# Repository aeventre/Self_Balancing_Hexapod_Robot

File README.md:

View this project on [CADLAB.io](https://cadlab.io/project/29567). 

# Self-Balancing Hexapod Robot
Created by: **Alec Ventresca & Ella Hicks**  

## Table of Contents
 - **[Self-Balancing Hexapod Robot](#self-balancing-hexapod-robot)**
   - [Overview](#overview)
   - [Future Ideas/Plans](#future-ideas)
   - [Acknowledgments](#acknowledgments) 
- [**Software Design**](ros2_ws/README.md)
  - [Overview](ros2_ws/README.md#overview)
  - [Instructions for Running the Software on the Pi](ros2_ws/README.md#instructions-for-running-the-software-on-the-pi)
    - [1. Setting Up the Virtual Environment](ros2_ws/README.md#1-setting-up-the-virtual-environment)
    - [2. Commands for Running Nodes](ros2_ws/README.md#2-commands-for-running-nodes)
  - [ROS2 Package Overview](ros2_ws/README.md#ros2-package-overview)
    - [1. Support Polygon Calculator](ros2_ws/README.md#1-support-polygon-calculator)
    - [2. Servo Control](ros2_ws/README.md#2-servo-control)
    - [3. IMU Interface](ros2_ws/README.md#3-imu-interface)
    - [4. Foot Sensor Package](ros2_ws/README.md#4-foot-sensor-package)
    - [5. Static Balancing Package](ros2_ws/README.md#5-static-balancing-package)
    - [6. Inverse and Forward Kinematics Package](ros2_ws/README.md#6-inverse-and-forward-kinematics-package)
    - [7. Center of Mass Calculator Package](ros2_ws/README.md#7-center-of-mass-calculator-package)
  - [ROS2 Topic List](ros2_ws/README.md#ros2-topic-list)
- [**Hardware Design**](hardware/README.md) 
  - [Overview](hardware/README.md#overview)
  - [Structure](hardware/README.md#structure)
  - [Electronics](hardware/README.md#electronics)
    - [Setting the I2C Address of the PCA9685](hardware/README.md#setting-the-i2c-address-of-the-pca9685)
  - [PCB Layout](hardware/README.md#pcb-layout)

## Overview
This robot was created to be a platform for us to learn and experiment with various types of sensors and gaits as well as learn the ROS2 framework. Modularity is a large component of this design, both hardware and software wise, so different sensors can be added and removed without needing to change the core design of the robot. Currently, this is just the foundation of the robot and we intend to add more sensor and package configurations in the future!  

The goal for the initial configuration of this project was to design a Hexapod Robot capable of performing dynamic movements and maintaining self-balance. The robot demonstrates the integration of mechanical and electronic systems and software packages to achieve autonomous and stable locomotion. The hexapod robot features a Raspberry Pi 4b as the central processing unit. It relies on ROS 2 Jazzy to manage the communication and control across the robot's various components. Each package communication ensures continuous data exchange between the packages for dynamic adjustments. The key objectives of the hexapod include the following:

1. Ensuring the robot can walk and move dynamically.
2. Incorporating real-time balancing mechanisms to keep the robot functional and upright under various conditions.
3. Develop modular software packages for control, movement computation, and sensing.
4. Utilize ROS 2 Jazzy to coordinate the robot's operations.

### Future Ideas
In no particular order:
1. Debugging the code and re-doing the math for the kinematics package to make it work efficiently.
2. Using a LiDAR sensor to map out a room for the robot.
3. Experimenting with different gaits (i.e. a quadruped "attack" mode).
4. Adding a Pi camera and learning opencv to have the robot recognize and go to people.
5. Implementing rough terrain navigation.

## Acknowledgments
All CAD models used are from "Robs Tech Workbench" at https://github.com/robs-tech-workbench/hexapod_spiderbot_model/
  
Shoutout to Addison Sears-Collins for all the incredibly helpful ROS2 tutorials at https://automaticaddison.com/

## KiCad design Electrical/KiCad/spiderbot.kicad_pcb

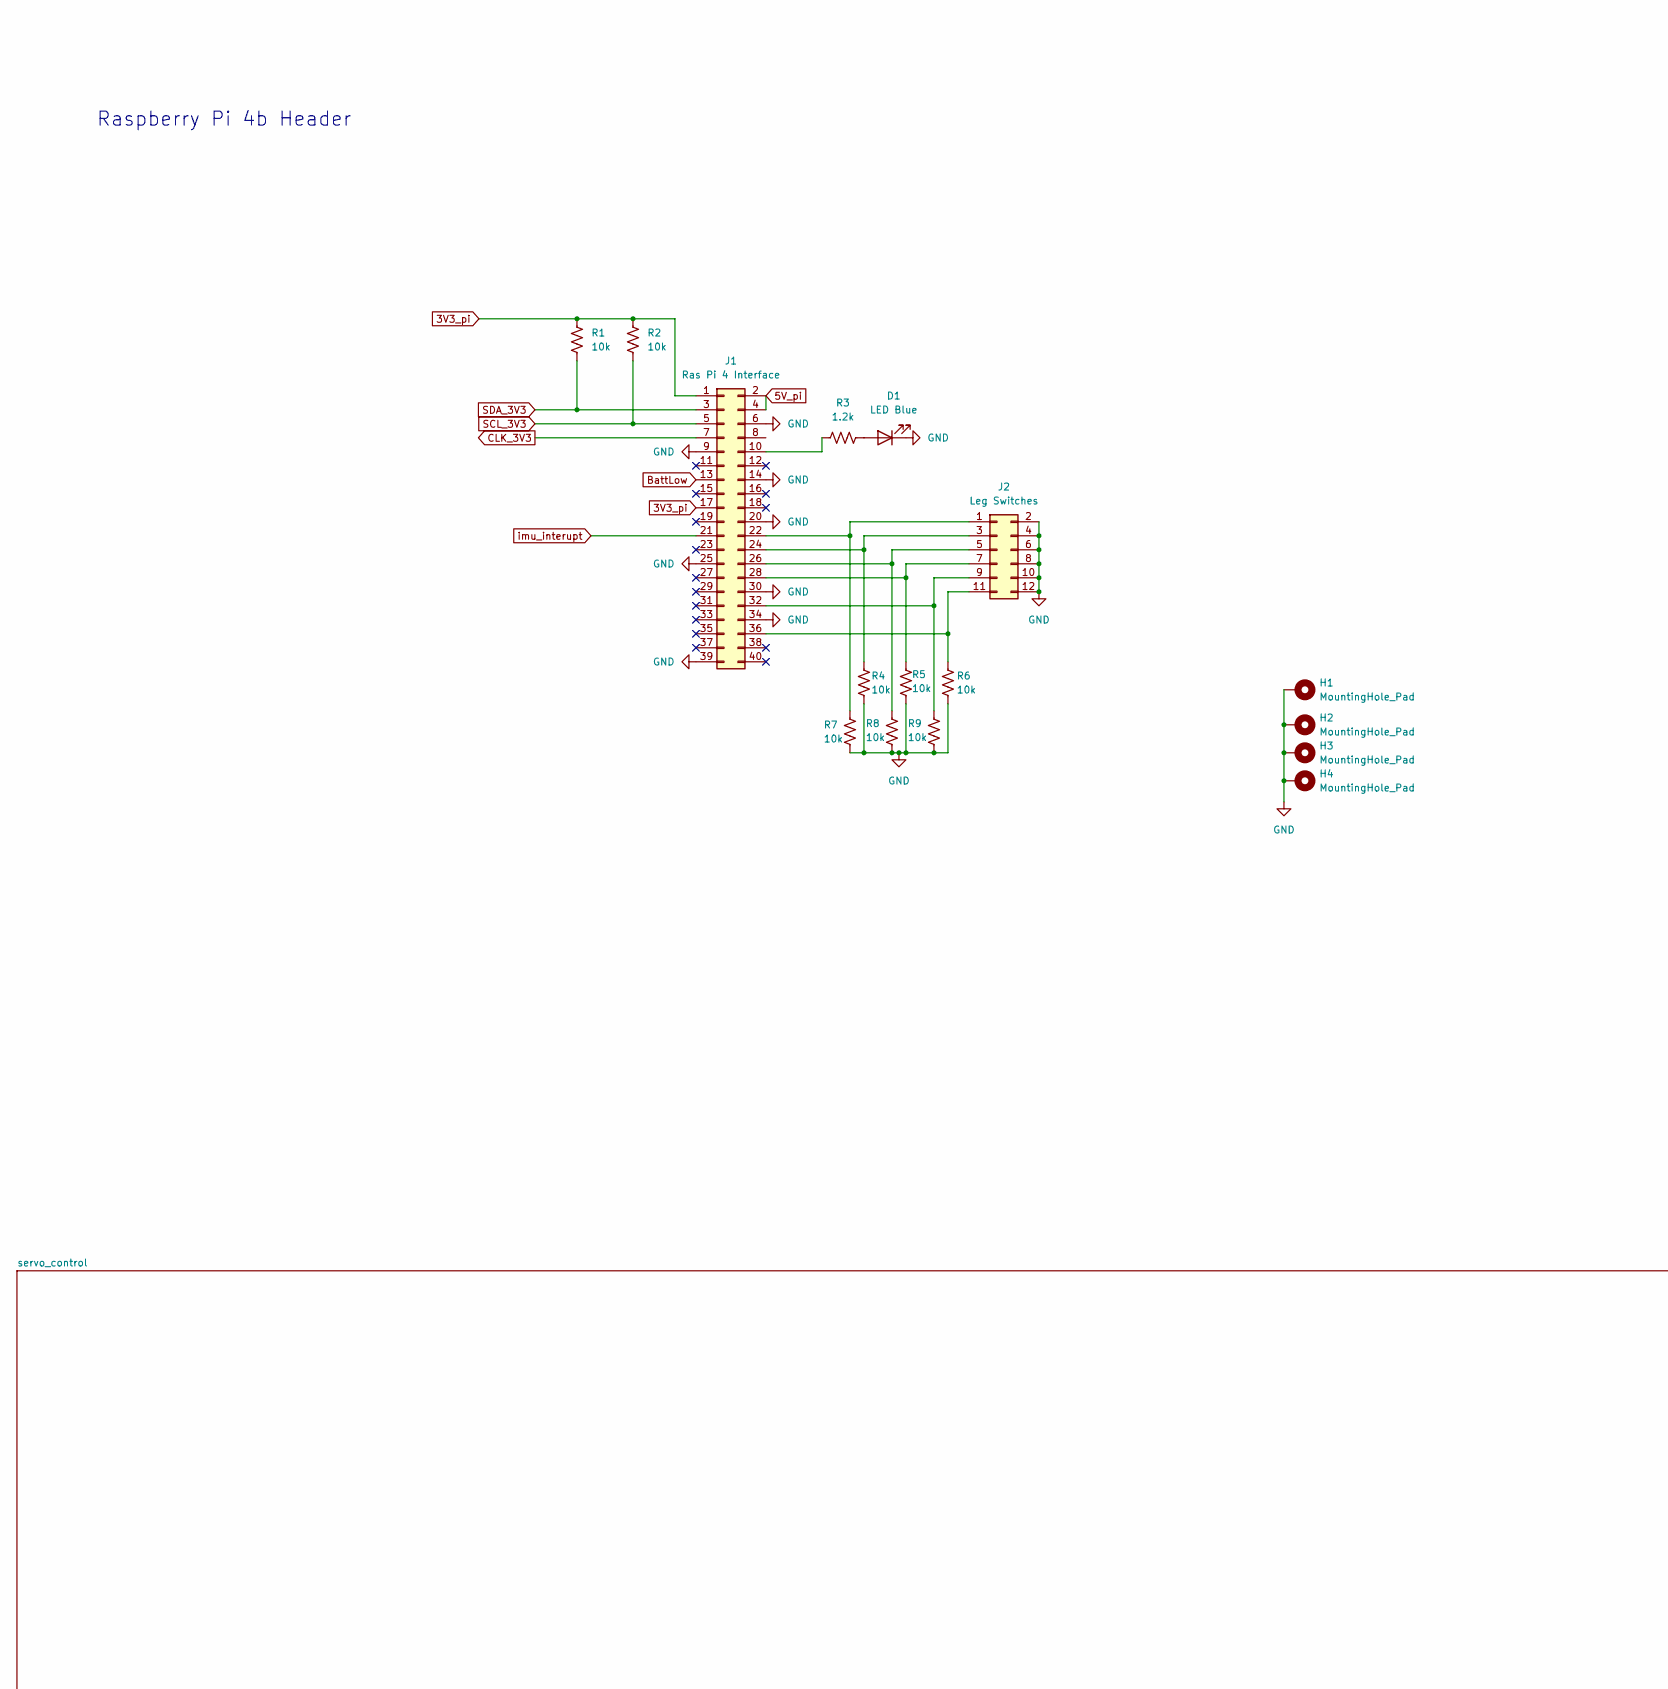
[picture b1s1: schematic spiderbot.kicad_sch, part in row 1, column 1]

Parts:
D1: LED Blue; LED_0603_1608Metric_Pad1.05x0.95mm_HandSolder; PART-NUMBER 1497-XZCFBB53W-8VFCT-ND
H1, H2, H3, H4: MountingHole_Pad; MountingHole_3.2mm_M3_DIN965_Pad_TopBottom
J1: Ras Pi 4 Interface; PinSocket_2x20_P2.54mm_Vertical; PART-NUMBER 1568-PRT-16764-ND
J2: Leg Switches; PinSocket_2x06_P2.54mm_Vertical
R1, R2, R4, R5, R6, R7, R8, R9: 10k; R_0603_1608Metric_Pad0.98x0.95mm_HandSolder; PART-NUMBER CPF0603F10KC1
R3: 1.2k; R_0603_1608Metric_Pad0.98x0.95mm_HandSolder; PART-NUMBER P1.2KDBCT-ND

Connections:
3V3_pi: J1.1, J1.17, R1.1, R2.1; also elsewhere on the board
5V_pi: J1.2, J1.4; also elsewhere on the board
BattLow: J1.13; also elsewhere on the board
CLK_3V3: J1.7; also elsewhere on the board
GND: D1.1 (K), H1.1, H2.1, H3.1, H4.1, J1.6, J1.9, J1.14, J1.20, J1.25, J1.30, J1.34, J1.39, J2.2, J2.4, J2.6, J2.8, J2.10, J2.12, R4.2, R5.2, R6.2, R7.2, R8.2, R9.2; also elsewhere on the board
unnamed: D1.2 (A), R3.1
unnamed: J1.10, R3.2
unnamed: J1.22, J2.1, R7.1
unnamed: J1.24, J2.3, R4.1
unnamed: J1.26, J2.5, R8.1
unnamed: J1.28, J2.7, R5.1
unnamed: J1.32, J2.9, R9.1
unnamed: J1.36, J2.11, R6.1
SCL_3V3: J1.5, R2.2; also elsewhere on the board
SDA_3V3: J1.3, R1.2; also elsewhere on the board
imu_interupt: J1.21; also elsewhere on the board

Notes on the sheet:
Raspberry Pi 4b Header

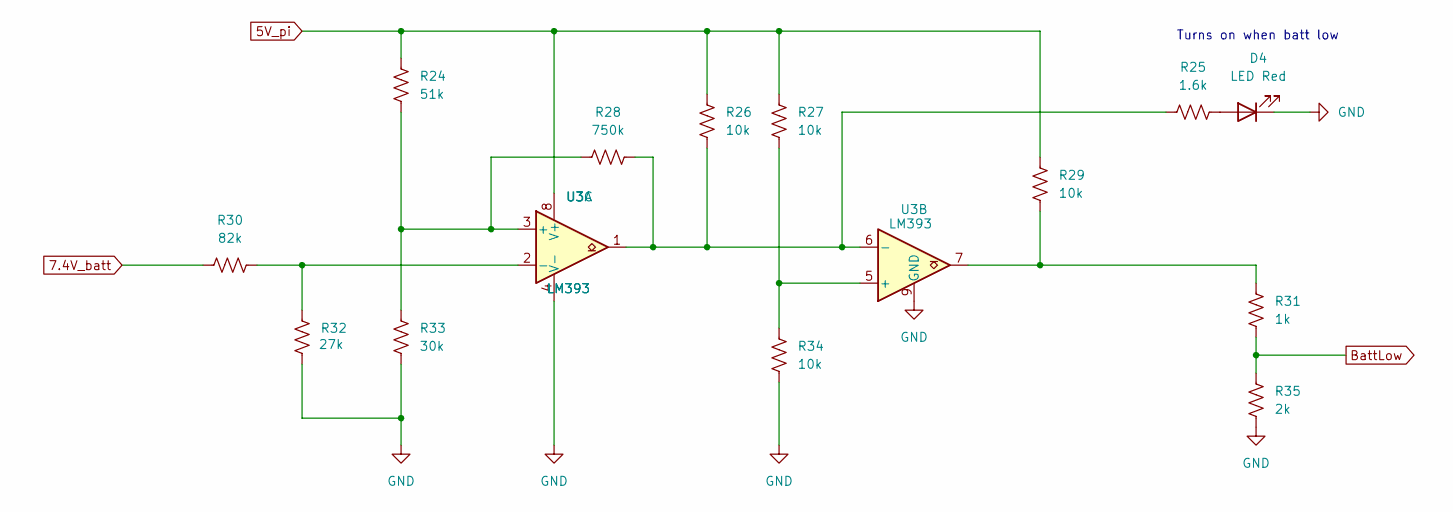
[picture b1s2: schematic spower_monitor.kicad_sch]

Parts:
D4: LED Red; LED_0603_1608Metric_Pad1.05x0.95mm_HandSolder
R24: 51k; R_0603_1608Metric_Pad0.98x0.95mm_HandSolder
R25: 1.6k; R_0603_1608Metric_Pad0.98x0.95mm_HandSolder
R26, R27, R29, R34: 10k; R_0603_1608Metric_Pad0.98x0.95mm_HandSolder
R28: 750k; R_0603_1608Metric_Pad0.98x0.95mm_HandSolder
R30: 82k; R_0603_1608Metric_Pad0.98x0.95mm_HandSolder
R31: 1k; R_0603_1608Metric_Pad0.98x0.95mm_HandSolder
R32: 27k; R_0603_1608Metric_Pad0.98x0.95mm_HandSolder
R33: 30k; R_0603_1608Metric_Pad0.98x0.95mm_HandSolder
R35: 2k; R_0603_1608Metric_Pad0.98x0.95mm_HandSolder
U3: LM393; SOIC-8-1EP_3.9x4.9mm_P1.27mm_EP2.29x3mm

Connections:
5V_pi: R24.1, R26.1, R27.1, R29.1, U3.8 (V+); also elsewhere on the board
7.4V_batt: R30.1; also elsewhere on the board
BattLow: R31.2, R35.2; also elsewhere on the board
GND: D4.1 (K), R32.2, R33.2, R34.2, R35.1, U3.4 (V-), U3.9 (GND); also elsewhere on the board
unnamed: D4.2 (A), R25.2
unnamed: R29.2, R31.1, U3.7
unnamed: R24.2, R28.1, R33.1, U3.3 (+)
unnamed: R30.2, R32.1, U3.2 (-)
unnamed: R27.2, R34.1, U3.5 (+)
unnamed: R25.1, R26.2, R28.2, U3.1, U3.6 (-)

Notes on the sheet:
Turns on when batt low

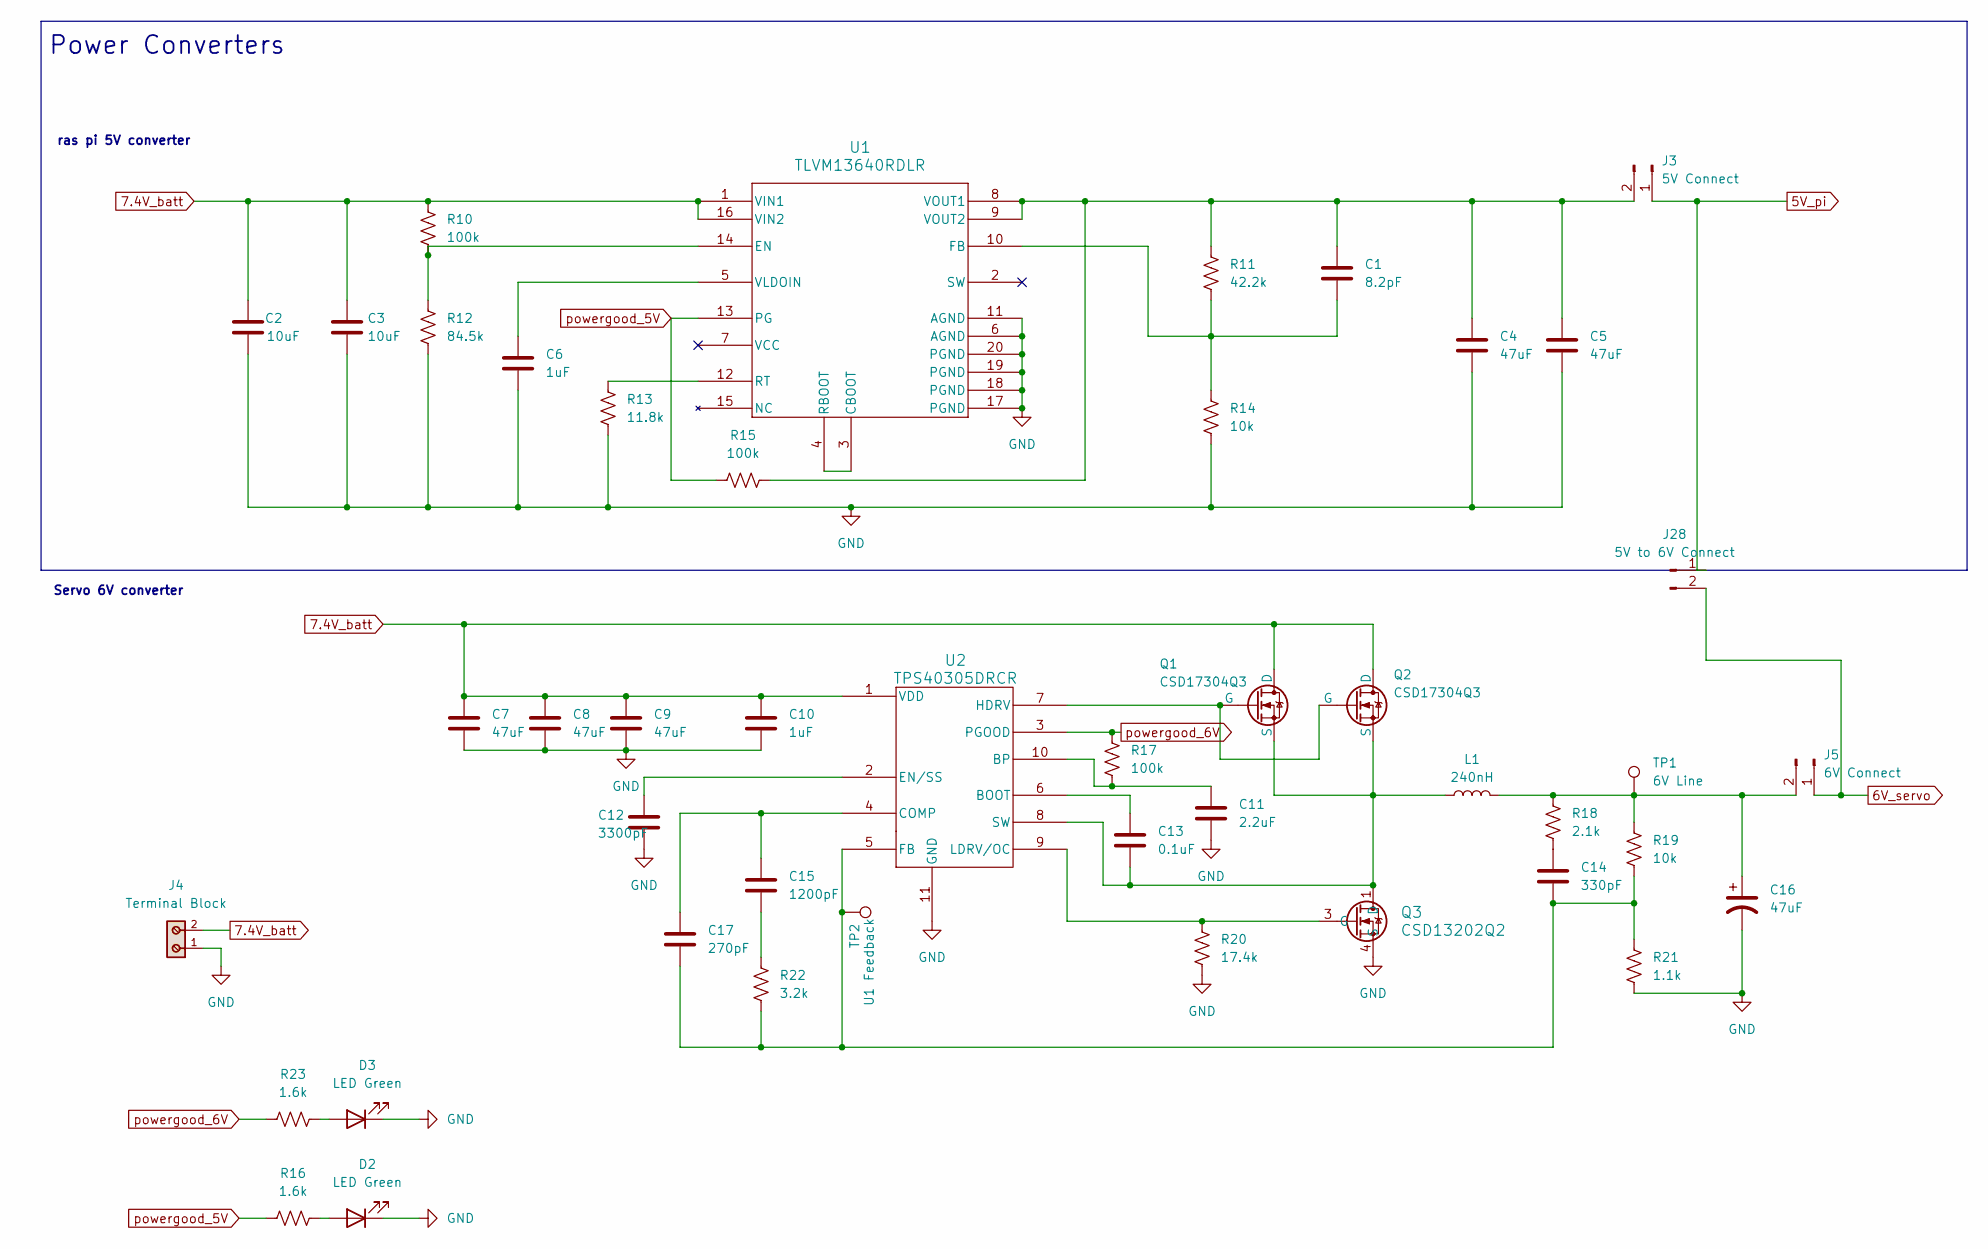
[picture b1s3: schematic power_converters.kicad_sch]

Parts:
C1: 8.2pF; C_0603_1608Metric_Pad1.08x0.95mm_HandSolder; PART-NUMBER CC0603CRNPO9BN8R2
C2, C3: 10uF; C_1210_3225Metric_Pad1.33x2.70mm_HandSolder; PART-NUMBER C3225X7R1H106M250AC
C4, C5, C7, C8, C9: 47uF; C_1210_3225Metric_Pad1.33x2.70mm_HandSolder; PART-NUMBER GRM32ER61C476KE15L
C6: 1uF; C_0603_1608Metric_Pad1.08x0.95mm_HandSolder; PART-NUMBER GRM188R60J105KA01D
C10: 1uF; C_0805_2012Metric_Pad1.18x1.45mm_HandSolder; PART-NUMBER TMK212BJ105KG-T
C11: 2.2uF; C_0805_2012Metric_Pad1.18x1.45mm_HandSolder; PART-NUMBER GRM21BR71A225KA01L
C12: 3300pF; C_0603_1608Metric_Pad1.08x0.95mm_HandSolder; PART-NUMBER CC0603KRX7R8BB332
C13: 0.1uF; C_0603_1608Metric_Pad1.08x0.95mm_HandSolder; PART-NUMBER C0603C104M3VACTU
C14: 330pF; C_0603_1608Metric_Pad1.08x0.95mm_HandSolder; PART-NUMBER CC0603KRX7R9BB331
C15: 1200pF; C_0805_2012Metric_Pad1.18x1.45mm_HandSolder; PART-NUMBER C2012C0G1H122J060AA
C16: 47uF; PCAP_TPE_B2_PAN_1411; PART-NUMBER 10TPE47MAZB
C17: 270pF; C_0603_1608Metric_Pad1.08x0.95mm_HandSolder; PART-NUMBER CL10C271JB81PNC
D2, D3: LED Green; LED_0603_1608Metric_Pad1.05x0.95mm_HandSolder; PART-NUMBER 1497-XZCDGK53W-8VFCT-ND
J3: 5V Connect; PinSocket_1x02_P2.54mm_Vertical; PART-NUMBER M20-9990245
J4: Terminal Block; TerminalBlock_MetzConnect_Type011_RT05502HBWC_1x02_P5.00mm_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; PART-NUMBER 691214110002
J5: 6V Connect; PinSocket_1x02_P2.54mm_Vertical; PART-NUMBER M20-9990245
J28: 5V to 6V Connect; PinSocket_1x02_P2.54mm_Vertical; PART-NUMBER M20-9990245
L1: 240nH; IND_IHLP-4040DZ_VIS; PART-NUMBER IHLP4040DZERR24M11
Q1, Q2: CSD17304Q3; 8VSON; PART-NUMBER CSD17304Q3
Q3: CSD13202Q2; Q2_SON6_TEX; PART-NUMBER CSD13202Q2
R10, R15, R17: 100k; R_0603_1608Metric_Pad0.98x0.95mm_HandSolder; PART-NUMBER CPF0603F100KC1
R11: 42.2k; R_0603_1608Metric_Pad0.98x0.95mm_HandSolder; PART-NUMBER CRCW060342K2FKEA
R12: 84.5k; R_0402_1005Metric_Pad0.72x0.64mm_HandSolder; PART-NUMBER CRCW040284K5FKED
R13: 11.8k; R_0603_1608Metric_Pad0.98x0.95mm_HandSolder; PART-NUMBER CPF0603F11K8C1
R14, R19: 10k; R_0603_1608Metric_Pad0.98x0.95mm_HandSolder; PART-NUMBER CPF0603F10KC1
R16, R23: 1.6k; R_0603_1608Metric_Pad0.98x0.95mm_HandSolder; PART-NUMBER 541-5237-1-ND
R18: 2.1k; R_0603_1608Metric_Pad0.98x0.95mm_HandSolder; PART-NUMBER RMCF0603FT2K10
R20: 17.4k; R_0402_1005Metric_Pad0.72x0.64mm_HandSolder; PART-NUMBER CRCW040217K4FKED
R21: 1.1k; R_0603_1608Metric_Pad0.98x0.95mm_HandSolder; PART-NUMBER CPF0603F1K1C1
R22: 3.2k; C_0805_2012Metric_Pad1.18x1.45mm_HandSolder; PART-NUMBER TNPW08053K20BEEA
TP1: 6V Line; TestPoint_Loop_D1.80mm_Drill1.0mm_Beaded
TP2: U1 Feedback; TestPoint_Loop_D1.80mm_Drill1.0mm_Beaded
U1: TLVM13640RDLR; B3QFN20_RDL_TEX; PART-NUMBER TLVM13640RDLR
U2: TPS40305DRCR; VSON-10-1EP_3x3mm_P0.5mm_EP1.2x2mm_ThermalVias; PART-NUMBER TPS40305DRCR

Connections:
5V_pi: J3.1, J28.1; also elsewhere on the board
6V_servo: J5.1, J28.2; also elsewhere on the board
7.4V_batt: C2.1, C3.1, C7.1, C8.1, C9.1, C10.1, J4.2, Q1.5 (D), Q1.6 (D), Q1.7 (D), Q1.8 (D), Q1.9 (D), Q2.5 (D), Q2.6 (D), Q2.7 (D), Q2.8 (D), Q2.9 (D), R10.1, U1.1 (VIN1), U1.16 (VIN2), U2.1 (VDD); also elsewhere on the board
GND: C2.2, C3.2, C4.2, C5.2, C6.2, C7.2, C8.2, C9.2, C10.2, C11.2, C12.2, C16.2, D2.1 (K), D3.1 (K), J4.1, Q3.4 (S), Q3.7 (S), R12.2, R13.2, R14.2, R20.2, R21.2, U1.6 (AGND), U1.11 (AGND), U1.17 (PGND), U1.18 (PGND), U1.19 (PGND), U1.20 (PGND), U2.11 (GND); also elsewhere on the board
unnamed: C14.1, R18.2
unnamed: C15.2, R22.1
unnamed: D2.2 (A), R16.2
unnamed: D3.2 (A), R23.2
unnamed: C1.1, C4.1, C5.1, J3.2, R11.1, R15.2, U1.8 (VOUT1), U1.9 (VOUT2)
unnamed: C16.1, J5.2, L1.2, R18.1, R19.1, TP1.1
unnamed: Q1.4 (G), Q2.4 (G), U2.7 (HDRV)
unnamed: Q3.3 (G), R20.1, U2.9 (LDRV/OC)
unnamed: U1.3 (CBOOT), U1.4 (RBOOT)
unnamed: R10.2, R12.1, U1.14 (EN)
unnamed: C1.2, R11.2, R14.1, U1.10 (FB)
unnamed: R13.1, U1.12 (RT)
unnamed: C6.1, U1.5 (VLDOIN)
unnamed: C13.1, U2.6 (BOOT)
unnamed: C11.1, R17.2, U2.10 (BP)
unnamed: C15.1, C17.1, U2.4 (COMP)
unnamed: C12.1, U2.2 (EN/SS)
unnamed: C14.2, C17.2, R19.2, R21.1, R22.2, TP2.1, U2.5 (FB)
unnamed: C13.2, L1.1, Q1.1 (S), Q1.2 (S), Q1.3 (S), Q2.1 (S), Q2.2 (S), Q2.3 (S), Q3.1 (D), Q3.2 (D), Q3.5 (D), Q3.6 (D), Q3.8 (D), U2.8 (SW)
powergood_5V: R15.1, R16.1, U1.13 (PG)
powergood_6V: R17.1, R23.1, U2.3 (PGOOD)

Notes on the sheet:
Power Converters
ras pi 5V converter
Servo 6V converter

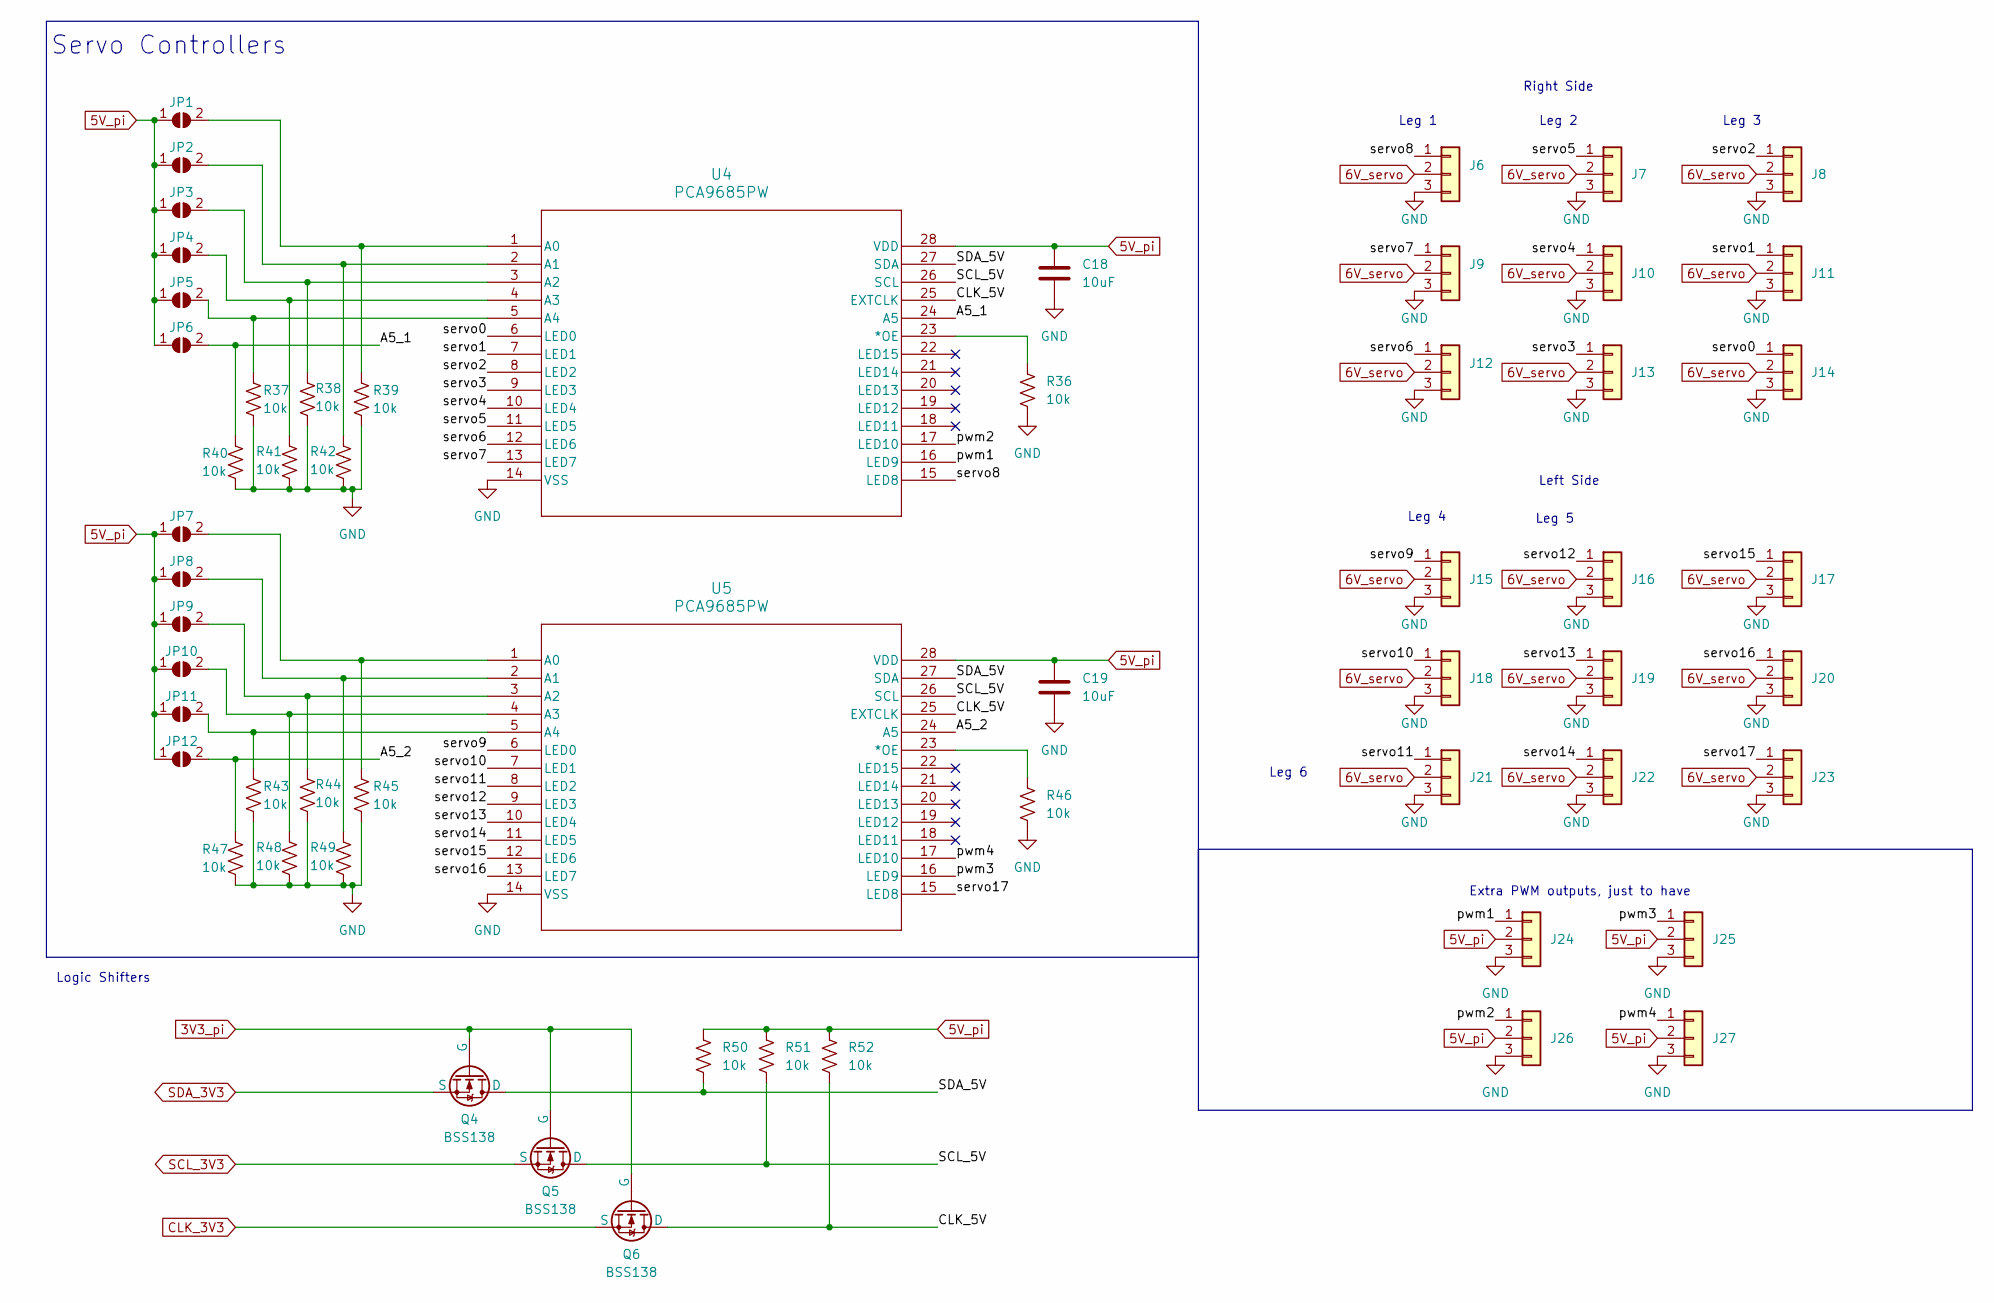
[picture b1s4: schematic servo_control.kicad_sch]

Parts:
C18, C19: 10uF; C_0603_1608Metric_Pad1.08x0.95mm_HandSolder; PART-NUMBER 1276-1192-1-ND
J6, J7, J8, J9, J10, J11, J12, J13, J14, J15, J16, J17, J18, J19, J20, J21, J22, J23, J24, J25, J26, J27: Conn_01x03; PinSocket_1x03_P2.54mm_Vertical; PART-NUMBER M20-9990345
JP1, JP2, JP3, JP4, JP5, JP6, JP7, JP8, JP9, JP10, JP11, JP12: SolderJumper_2_Open; R_0603_1608Metric_Pad0.98x0.95mm_HandSolder
Q4, Q5, Q6: BSS138; SOT-23_3L_ONS; PART-NUMBER BSS138CT-ND
R36, R37, R38, R39, R40, R41, R42, R43, R44, R45, R46, R47, R48, R49, R50, R51, R52: 10k; R_0603_1608Metric_Pad0.98x0.95mm_HandSolder; PART-NUMBER CPF0603F10KC1
U4, U5: PCA9685PW; SOT361-1_NXP; PART-NUMBER 568-8366-5-ND

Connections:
3V3_pi: Q4.2 (G), Q5.2 (G), Q6.2 (G); also elsewhere on the board
5V_pi: C18.1, C19.1, J24.2, J25.2, J26.2, J27.2, JP1.1 (A), JP2.1 (A), JP3.1 (A), JP4.1 (A), JP5.1 (A), JP6.1 (A), JP7.1 (A), JP8.1 (A), JP9.1 (A), JP10.1 (A), JP11.1 (A), JP12.1 (A), R50.1, R51.1, R52.1, U4.28 (VDD), U5.28 (VDD); also elsewhere on the board
6V_servo: J6.2, J7.2, J8.2, J9.2, J10.2, J11.2, J12.2, J13.2, J14.2, J15.2, J16.2, J17.2, J18.2, J19.2, J20.2, J21.2, J22.2, J23.2; also elsewhere on the board
/servo_control/A5_1: JP6.2 (B), R40.1, U4.24 (A5)
/servo_control/A5_2: JP12.2 (B), R47.1, U5.24 (A5)
/servo_control/CLK_5V: Q6.1 (D), R52.2, U4.25 (EXTCLK), U5.25 (EXTCLK)
/servo_control/SCL_5V: Q5.1 (D), R51.2, U4.26 (SCL), U5.26 (SCL)
/servo_control/SDA_5V: Q4.1 (D), R50.2, U4.27 (SDA), U5.27 (SDA)
/servo_control/pwm1: J24.1, U4.16 (LED9)
/servo_control/pwm2: J26.1, U4.17 (LED10)
/servo_control/pwm3: J25.1, U5.16 (LED9)
/servo_control/pwm4: J27.1, U5.17 (LED10)
/servo_control/servo0: J14.1, U4.6 (LED0)
/servo_control/servo1: J11.1, U4.7 (LED1)
/servo_control/servo2: J8.1, U4.8 (LED2)
/servo_control/servo3: J13.1, U4.9 (LED3)
/servo_control/servo4: J10.1, U4.10 (LED4)
/servo_control/servo5: J7.1, U4.11 (LED5)
/servo_control/servo6: J12.1, U4.12 (LED6)
/servo_control/servo7: J9.1, U4.13 (LED7)
/servo_control/servo8: J6.1, U4.15 (LED8)
/servo_control/servo9: J15.1, U5.6 (LED0)
/servo_control/servo10: J18.1, U5.7 (LED1)
/servo_control/servo11: J21.1, U5.8 (LED2)
/servo_control/servo12: J16.1, U5.9 (LED3)
/servo_control/servo13: J19.1, U5.10 (LED4)
/servo_control/servo14: J22.1, U5.11 (LED5)
/servo_control/servo15: J17.1, U5.12 (LED6)
/servo_control/servo16: J20.1, U5.13 (LED7)
/servo_control/servo17: J23.1, U5.15 (LED8)
CLK_3V3: Q6.3 (S); also elsewhere on the board
GND: C18.2, C19.2, J6.3, J7.3, J8.3, J9.3, J10.3, J11.3, J12.3, J13.3, J14.3, J15.3, J16.3, J17.3, J18.3, J19.3, J20.3, J21.3, J22.3, J23.3, J24.3, J25.3, J26.3, J27.3, R36.2, R37.2, R38.2, R39.2, R40.2, R41.2, R42.2, R43.2, R44.2, R45.2, R46.2, R47.2, R48.2, R49.2, U4.14 (VSS), U5.14 (VSS); also elsewhere on the board
unnamed: JP1.2 (B), R39.1, U4.1 (A0)
unnamed: JP2.2 (B), R42.1, U4.2 (A1)
unnamed: JP3.2 (B), R38.1, U4.3 (A2)
unnamed: JP4.2 (B), R41.1, U4.4 (A3)
unnamed: JP5.2 (B), R37.1, U4.5 (A4)
unnamed: JP7.2 (B), R45.1, U5.1 (A0)
unnamed: JP8.2 (B), R49.1, U5.2 (A1)
unnamed: JP9.2 (B), R44.1, U5.3 (A2)
unnamed: JP10.2 (B), R48.1, U5.4 (A3)
unnamed: JP11.2 (B), R43.1, U5.5 (A4)
unnamed: R36.1, U4.23 (*OE)
unnamed: R46.1, U5.23 (*OE)
SCL_3V3: Q5.3 (S); also elsewhere on the board
SDA_3V3: Q4.3 (S); also elsewhere on the board

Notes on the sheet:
Leg 3
Leg 2
Extra PWM outputs, just to have
Right Side
Leg 6
Logic Shifters
Leg 4
Leg 5
Left Side
Leg 1
Servo Controllers

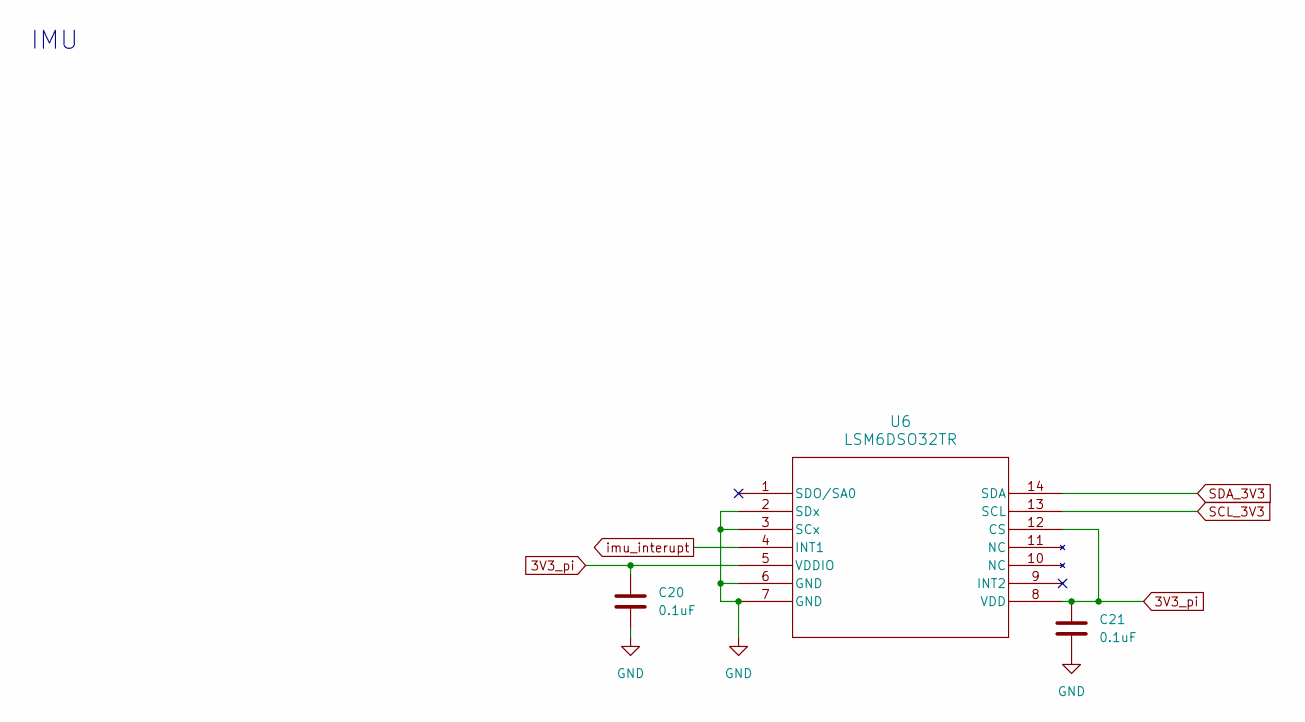
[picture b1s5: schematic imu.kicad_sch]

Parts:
C20, C21: 0.1uF; C_0603_1608Metric_Pad1.08x0.95mm_HandSolder; PART-NUMBER C0603C104M3VACTU
U6: LSM6DSO32TR; LGA-14L_2P5X3X0P83_STM; PART-NUMBER 497-LSM6DSO32CT-ND

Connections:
3V3_pi: C20.1, C21.1, U6.5 (VDDIO), U6.8 (VDD), U6.12 (CS); also elsewhere on the board
GND: C20.2, C21.2, U6.2 (SDx), U6.3 (SCx), U6.6 (GND), U6.7 (GND); also elsewhere on the board
SCL_3V3: U6.13 (SCL); also elsewhere on the board
SDA_3V3: U6.14 (SDA); also elsewhere on the board
imu_interupt: U6.4 (INT1); also elsewhere on the board

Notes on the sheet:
IMU

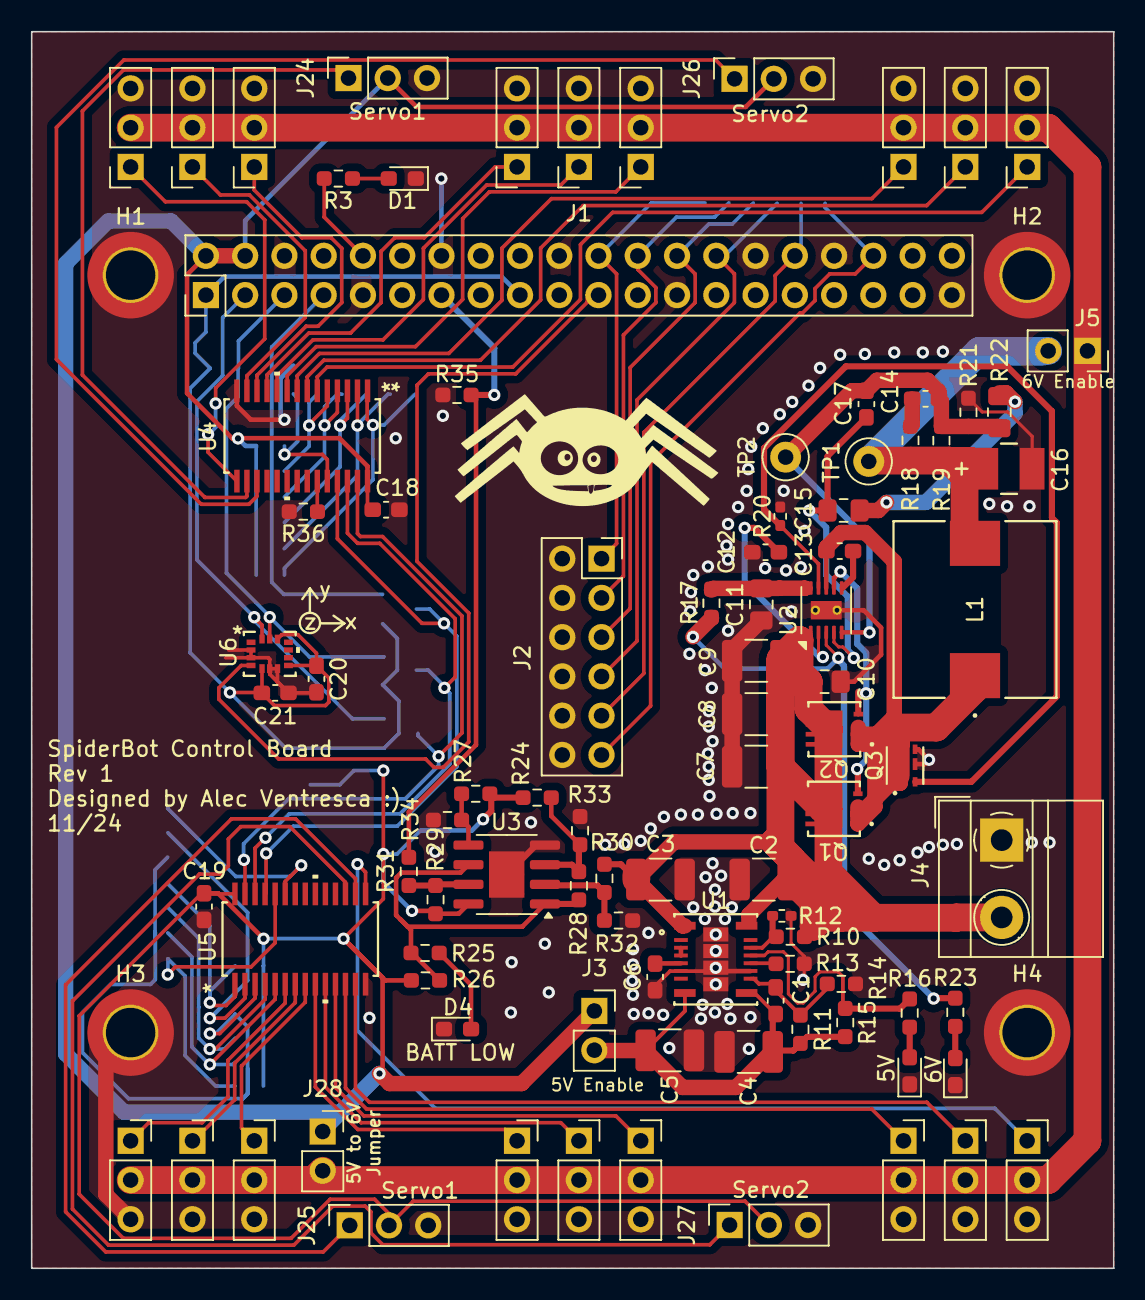
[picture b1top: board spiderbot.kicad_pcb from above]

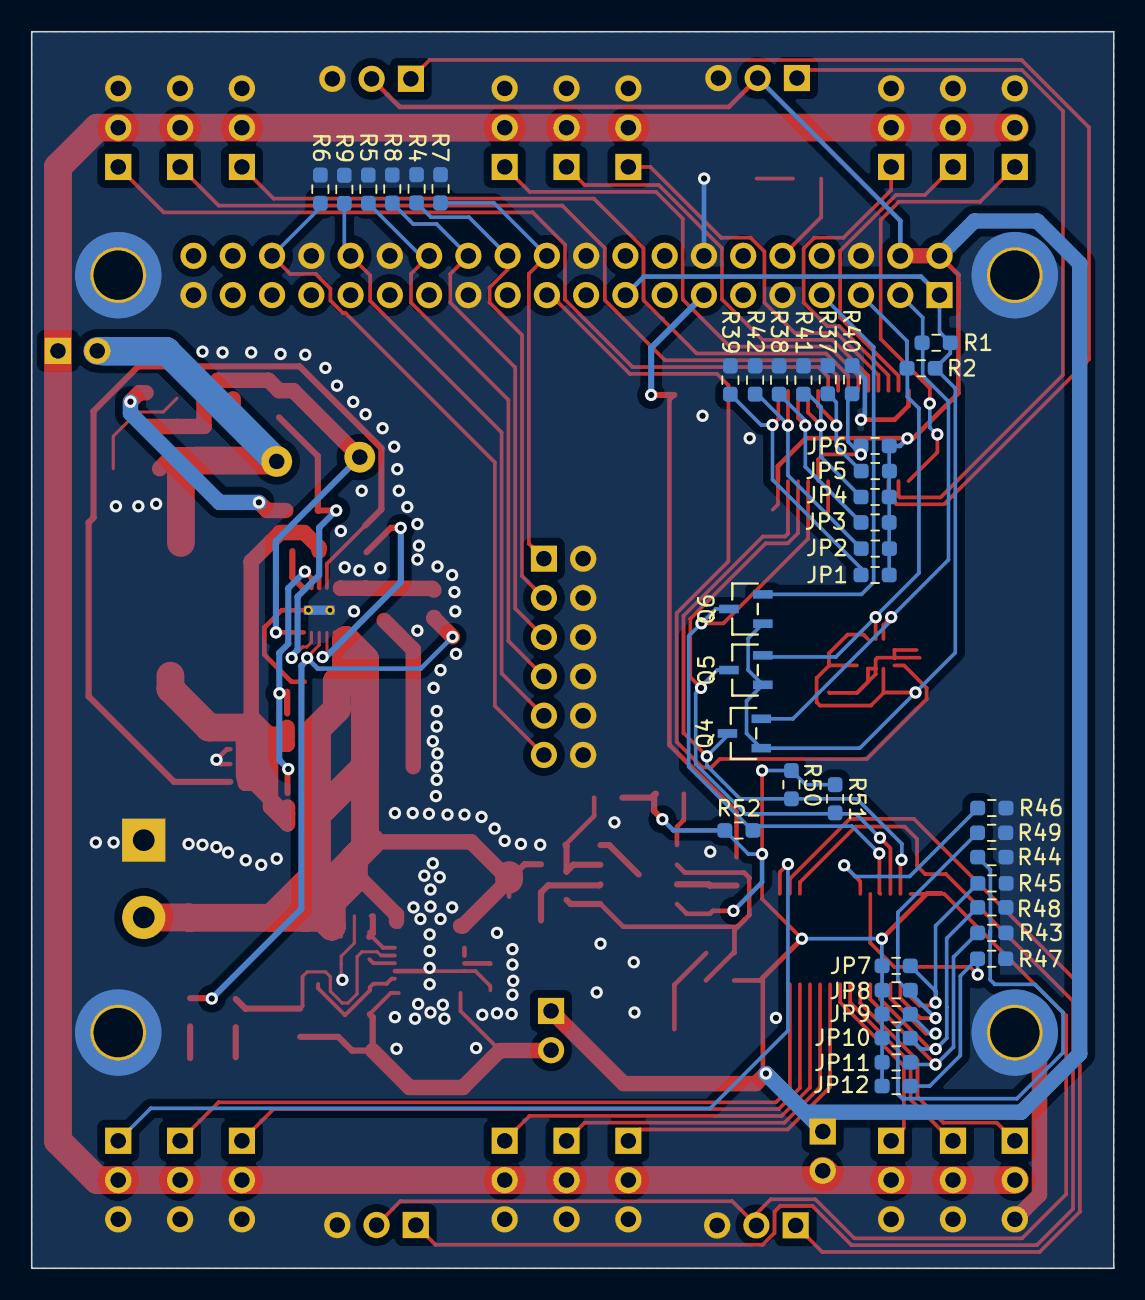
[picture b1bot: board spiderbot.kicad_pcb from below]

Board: 2 copper layers, 70.0 x 80.0 mm, 136 parts (39 on the bottom side), 84 nets.

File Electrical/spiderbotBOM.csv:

"Reference","Value","PART-NUMBER","Footprint","Qty"
"C1","8.2pF","CC0603CRNPO9BN8R2","Capacitor_SMD:C_0603_1608Metric_Pad1.08x0.95mm_HandSolder","1"
"C2,C3","10uF","C3225X7R1H106M250AC","Capacitor_SMD:C_1210_3225Metric_Pad1.33x2.70mm_HandSolder","2"
"C4,C5,C7,C8,C9","47uF","GRM32ER61C476KE15L","Capacitor_SMD:C_1210_3225Metric_Pad1.33x2.70mm_HandSolder","5"
"C6","1uF","GRM188R60J105KA01D","Capacitor_SMD:C_0603_1608Metric_Pad1.08x0.95mm_HandSolder","1"
"C10","1uF","TMK212BJ105KG-T","Capacitor_SMD:C_0805_2012Metric_Pad1.18x1.45mm_HandSolder","1"
"C11","2.2uF","GRM21BR71A225KA01L","Capacitor_SMD:C_0805_2012Metric_Pad1.18x1.45mm_HandSolder","1"
"C12","3300pF","CC0603KRX7R8BB332","Capacitor_SMD:C_0603_1608Metric_Pad1.08x0.95mm_HandSolder","1"
"C13,C20,C21","0.1uF","C0603C104M3VACTU","Capacitor_SMD:C_0603_1608Metric_Pad1.08x0.95mm_HandSolder","3"
"C14","330pF","CC0603KRX7R9BB331","Capacitor_SMD:C_0603_1608Metric_Pad1.08x0.95mm_HandSolder","1"
"C15","1200pF","C2012C0G1H122J060AA","Capacitor_SMD:C_0805_2012Metric_Pad1.18x1.45mm_HandSolder","1"
"C16","47uF","10TPE47MAZB","Spiderbot:PCAP_TPE_B2_PAN_1411","1"
"C17","270pF","CL10C271JB81PNC","Capacitor_SMD:C_0603_1608Metric_Pad1.08x0.95mm_HandSolder","1"
"C18,C19","10uF","1276-1192-1-ND","Capacitor_SMD:C_0603_1608Metric_Pad1.08x0.95mm_HandSolder","2"
"D1","LED Blue","1497-XZCFBB53W-8VFCT-ND","LED_SMD:LED_0603_1608Metric_Pad1.05x0.95mm_HandSolder","1"
"D2,D3","LED Green","1497-XZCDGK53W-8VFCT-ND","LED_SMD:LED_0603_1608Metric_Pad1.05x0.95mm_HandSolder","2"
"D4","LED Red","1497-XZCM2CRK53WA-8VFCT-ND","LED_SMD:LED_0603_1608Metric_Pad1.05x0.95mm_HandSolder","1"
"J1","Ras Pi 4 Interface","1568-PRT-16764-ND","Connector_PinSocket_2.54mm:PinSocket_2x20_P2.54mm_Vertical","1"
"J2,JP1,JP2,JP3,JP4,JP5,JP6,JP7,JP8,JP9,JP10,JP11,JP12,TP1,TP2","-- mixed values --","","-- mixed values --","15"
"J3,J5,J28","-- mixed values --","M20-9990245","Connector_PinSocket_2.54mm:PinSocket_1x02_P2.54mm_Vertical","3"
"J4","Terminal Block","691214110002","TerminalBlock_MetzConnect:TerminalBlock_MetzConnect_Type011_RT05502HBWC_1x02_P5.00mm_Horizontal","1"
"J6,J7,J8,J9,J10,J11,J12,J13,J14,J15,J16,J17,J18,J19,J20,J21,J22,J23,J24,J25,J26,J27","Conn_01x03","M20-9990345","Connector_PinSocket_2.54mm:PinSocket_1x03_P2.54mm_Vertical","22"
"L1","240nH","IHLP4040DZERR24M11","Spiderbot:IND_IHLP-4040DZ_VIS","1"
"Q1,Q2","CSD17304Q3","CSD17304Q3","Spiderbot:8VSON","2"
"Q3","CSD13202Q2","CSD13202Q2","Spiderbot:Q2_SON6_TEX","1"
"Q4,Q5,Q6","BSS138","BSS138CT-ND","Spiderbot:SOT-23_3L_ONS","3"
"R1,R2,R4,R5,R6,R7,R8,R9,R14,R19,R26,R27,R29,R34,R36,R37,R38,R39,R40,R41,R42,R43,R44,R45,R46,R47,R48,R49,R50,R51,R52","10k","CPF0603F10KC1","Resistor_SMD:R_0603_1608Metric_Pad0.98x0.95mm_HandSolder","31"
"R3","1.2k","P1.2KDBCT-ND","Resistor_SMD:R_0603_1608Metric_Pad0.98x0.95mm_HandSolder","1"
"R10,R15,R17","100k","CPF0603F100KC1","Resistor_SMD:R_0603_1608Metric_Pad0.98x0.95mm_HandSolder","3"
"R11","42.2k","CRCW060342K2FKEA","Resistor_SMD:R_0603_1608Metric_Pad0.98x0.95mm_HandSolder","1"
"R12","84.5k","CRCW040284K5FKED","Resistor_SMD:R_0402_1005Metric_Pad0.72x0.64mm_HandSolder","1"
"R13","11.8k","CPF0603F11K8C1","Resistor_SMD:R_0603_1608Metric_Pad0.98x0.95mm_HandSolder","1"
"R16,R23,R25","1.6k","541-5237-1-ND","Resistor_SMD:R_0603_1608Metric_Pad0.98x0.95mm_HandSolder","3"
"R18","2.1k","RMCF0603FT2K10","Resistor_SMD:R_0603_1608Metric_Pad0.98x0.95mm_HandSolder","1"
"R20","17.4k","CRCW040217K4FKED","Resistor_SMD:R_0402_1005Metric_Pad0.72x0.64mm_HandSolder","1"
"R21","1.1k","CPF0603F1K1C1","Resistor_SMD:R_0603_1608Metric_Pad0.98x0.95mm_HandSolder","1"
"R22","3.2k","TNPW08053K20BEEA","Capacitor_SMD:C_0805_2012Metric_Pad1.18x1.45mm_HandSolder","1"
"R24","51k","RC0603FR-0751KL","Resistor_SMD:R_0603_1608Metric_Pad0.98x0.95mm_HandSolder","1"
"R28","750k","RMCF0603FT750K","Resistor_SMD:R_0603_1608Metric_Pad0.98x0.95mm_HandSolder","1"
"R30","82k","RC0603JR-0782KL","Resistor_SMD:R_0603_1608Metric_Pad0.98x0.95mm_HandSolder","1"
"R31","1k","RC0603FR-071KL","Resistor_SMD:R_0603_1608Metric_Pad0.98x0.95mm_HandSolder","1"
"R32","27k","RMCF0603FT27K4","Resistor_SMD:R_0603_1608Metric_Pad0.98x0.95mm_HandSolder","1"
"R33","30k","ERA-3AEB303V","Resistor_SMD:R_0603_1608Metric_Pad0.98x0.95mm_HandSolder","1"
"R35","2k","ERA-3AEB202V","Resistor_SMD:R_0603_1608Metric_Pad0.98x0.95mm_HandSolder","1"
"U1","TLVM13640RDLR","TLVM13640RDLR","Spiderbot:B3QFN20_RDL_TEX","1"
"U2","TPS40305DRCR","TPS40305DRCR","Package_SON:VSON-10-1EP_3x3mm_P0.5mm_EP1.2x2mm_ThermalVias","1"
"U3","LM393","296-1015-1-ND","Package_SO:SOIC-8-1EP_3.9x4.9mm_P1.27mm_EP2.29x3mm","1"
"U4,U5","PCA9685PW","568-8366-5-ND","Spiderbot:SOT361-1_NXP","2"
"U6","LSM6DSO32TR","497-LSM6DSO32CT-ND","Spiderbot:LGA-14L_2P5X3X0P83_STM","1"
